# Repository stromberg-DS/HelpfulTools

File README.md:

# HelpfulTools
Helpful tools and examples for coding. Geared towards Explora folks with limited coding knowledge.

## Folder Info
### PhotonBreakout
These are the files to get more Photon Breakout PCBs made. There are files that can be opened in KiCAD if you want to change things. If you just need more PCBs, upload **PhotonBreakout-B_Mask.zip** to a PCB manufacturer such as PCBway.com.

### Adafruit_Publish_Subscribe
This is example code of how to publish to an Adafruit.io dashboard or subscribe to an Adafruit.io feed.

### I2C_Scan
A simple program that tells you the address of whatever I2C devices are hooked up.

### NeoPix_ColorPicker
Use this program and a neopixel LED strip to get the Hex codes of colors that you want.

### Neopixel_Basics
Here are the fundamentals to getting neopixels (WS2812) to work.

### Reset_Add_Wifi
Here is basic code to add new wifi networks.

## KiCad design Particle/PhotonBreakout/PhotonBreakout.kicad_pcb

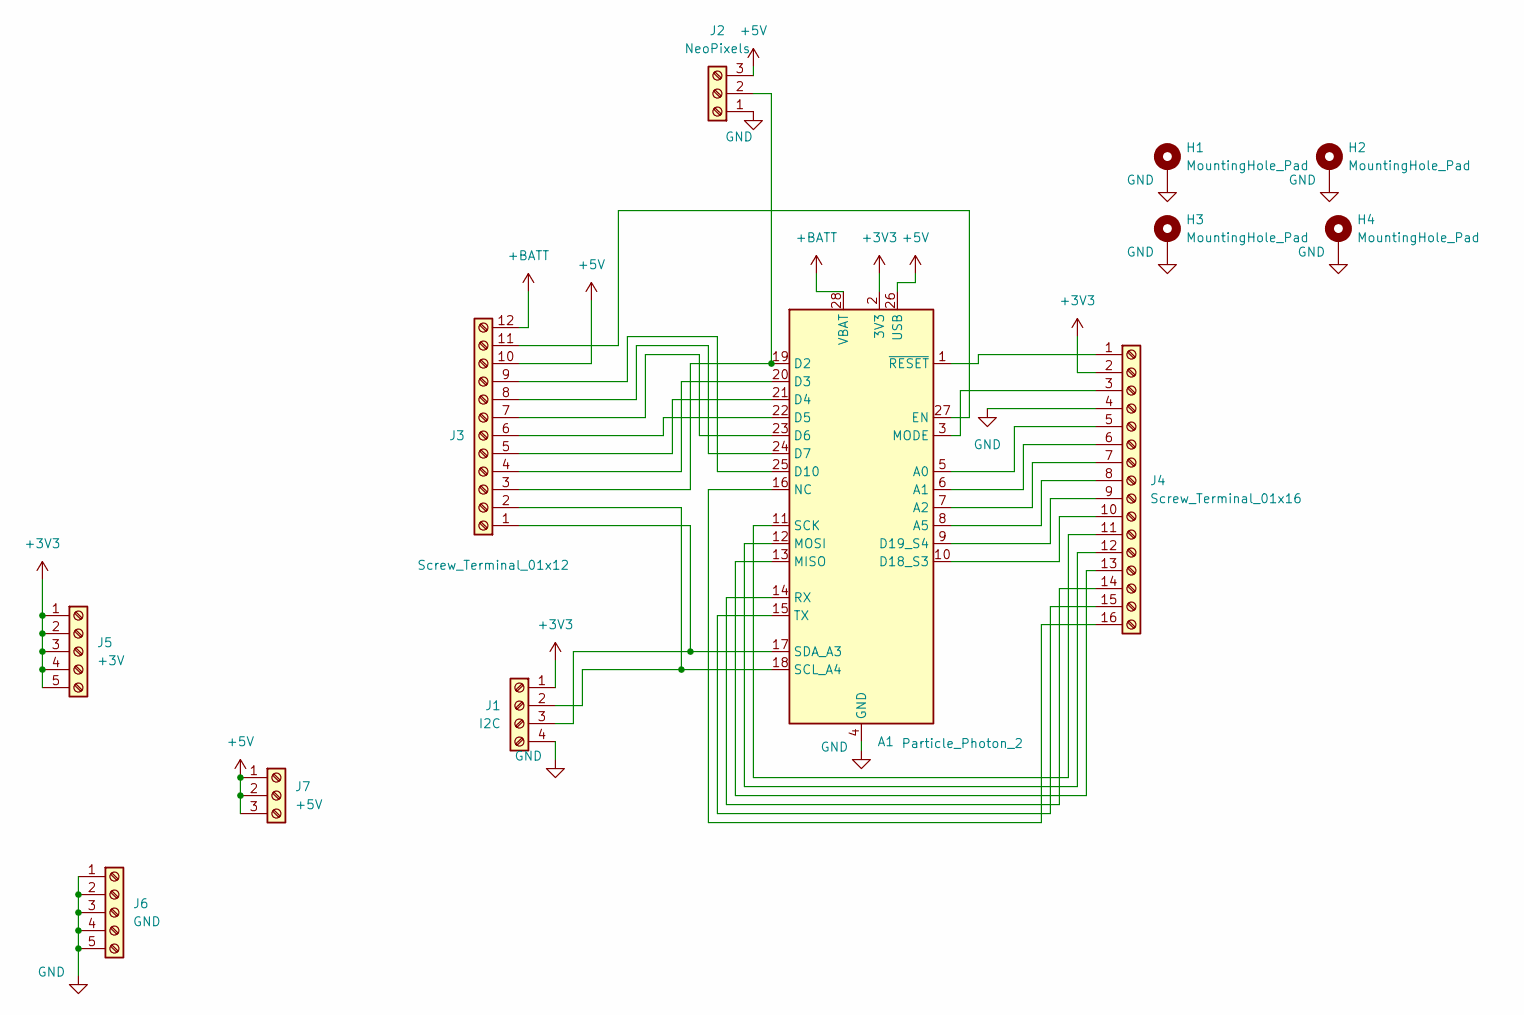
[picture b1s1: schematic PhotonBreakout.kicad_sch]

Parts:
A1: Particle_Photon_2; Photon_2
H1, H2, H3, H4: MountingHole_Pad; MountingHole_3.7mm_Pad_Via
J1: I2C; TerminalBlock_Phoenix_MPT-0,5-4-2.54_1x04_P2.54mm_Horizontal
J2: NeoPixels; TerminalBlock_Phoenix_MPT-0,5-3-2.54_1x03_P2.54mm_Horizontal
J3: Screw_Terminal_01x12; TerminalBlock_Phoenix_MPT-0,5-12-2.54_1x12_P2.54mm_Horizont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
J4: Screw_Terminal_01x16; TerminalBlock_Xinya_XY308-2.54-16P_1x16_P2.54mm_Horizontal
J5: +3V; TerminalBlock_Phoenix_MPT-0,5-5-2.54_1x05_P2.54mm_Horizontal
J6: GND; TerminalBlock_Phoenix_MPT-0,5-5-2.54_1x05_P2.54mm_Horizontal
J7: +5V; TerminalBlock_Phoenix_MPT-0,5-3-2.54_1x03_P2.54mm_Horizontal

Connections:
+3V3: A1.2 (3V3), J1.1, J4.2, J5.1, J5.2, J5.3, J5.4, J5.5
+5V: A1.26 (USB), J2.3, J3.10, J7.1, J7.2, J7.3
+BATT: A1.28 (VBAT), J3.12
GND: A1.4 (GND), H1.1, H2.1, H3.1, H4.1, J1.4, J2.1, J4.4, J6.1, J6.2, J6.3, J6.4, J6.5
unnamed: A1.5 (A0), J4.5
unnamed: A1.6 (A1), J4.6
unnamed: A1.7 (A2), J4.7
unnamed: A1.8 (A5), J4.8
unnamed: A1.19 (D2), J2.2, J3.3
unnamed: A1.20 (D3), J3.4
unnamed: A1.21 (D4), J3.5
unnamed: A1.22 (D5), J3.6
unnamed: A1.23 (D6), J3.7
unnamed: A1.24 (D7), J3.8
unnamed: A1.25 (D10), J3.9
unnamed: A1.10 (D18_S3), J4.10
unnamed: A1.9 (D19_S4), J4.9
unnamed: A1.27 (EN), J3.11
unnamed: A1.13 (MISO), J4.13
unnamed: A1.3 (MODE), J4.3
unnamed: A1.12 (MOSI), J4.12
unnamed: A1.16 (NC), J4.16
unnamed: A1.14 (RX), J4.14
unnamed: A1.11 (SCK), J4.11
unnamed: A1.18 (SCL_A4), J1.2, J3.2
unnamed: A1.17 (SDA_A3), J1.3, J3.1
unnamed: A1.15 (TX), J4.15
unnamed: A1.1 (~RESET), J4.1

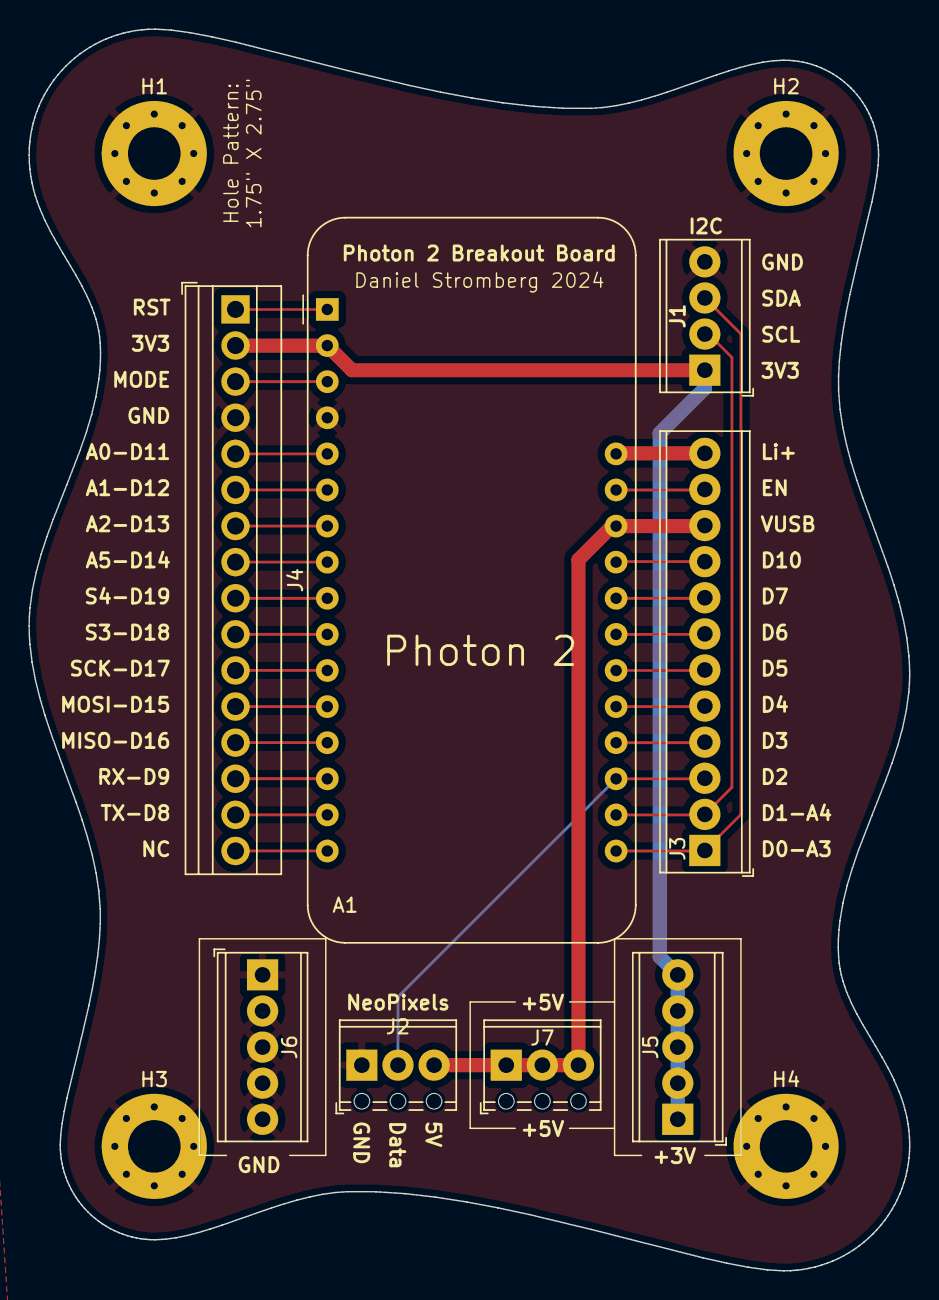
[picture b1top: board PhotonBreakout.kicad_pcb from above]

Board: 2 copper layers, 62.0 x 87.4 mm, 12 parts (0 on the bottom side), 28 nets.

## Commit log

2024-04-22 Added some basics
2024-04-22 changed semi-automatic to automatic
2024-04-23 Added Wifi Reset code
2024-06-07 Added Adafruit publish and subscribe example.
2024-06-07 updated gitignore
2024-09-19 Added KiCAD files for Photon 2 breakout board
2024-09-30 old update
2024-10-12 Cleaned up for comparing 2 colors to each other.
